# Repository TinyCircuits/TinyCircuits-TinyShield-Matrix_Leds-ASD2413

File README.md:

# TinyCircuits TinyShield Matrix LEDs
# ASD2413 Rev2

The design files are located under design_files/ for the TinyCircuits ASD2413 Rev 2 PCB.  This is a Tiny shield board (Square Version, 20mm x 20mm) that has a 54 LEDs in a 6x9 Matrix.

Format is in Cadsoft Eagle format - Eagle version 6.2 was used for the original design.

For more infomation on this, check out the product page at TinyCircuits.com:  https://tinycircuits.com/collections/leds-displays/products/matrix-led-tinyshield

# License:

Design by TinyCircuits.
All design files are released under the Creative Commons Attribution Share-Alike 3.0 License, see the following link for details: http://creativecommons.org/licenses/by-sa/3.0

All text above must be included in any redistribution or derived design

This project uses designs and concepts developed as part of the Arduino project and the LilyPad project.  The TinyCircuits design files themselves (schematics, PCB and libraries) are not directly derived from these works' design files and have been created new, however the concepts and basic architecture behind the TinyDuino and TinyLily products are derived and we thank the hard work of the organizations below for their contributions to open-source hardware:
  
Original Arduino Uno Design by Team Arduino

LilyPad Arduino Design by Leah Buechley and Sparkfun Electronics

Please support the open-source hardware community

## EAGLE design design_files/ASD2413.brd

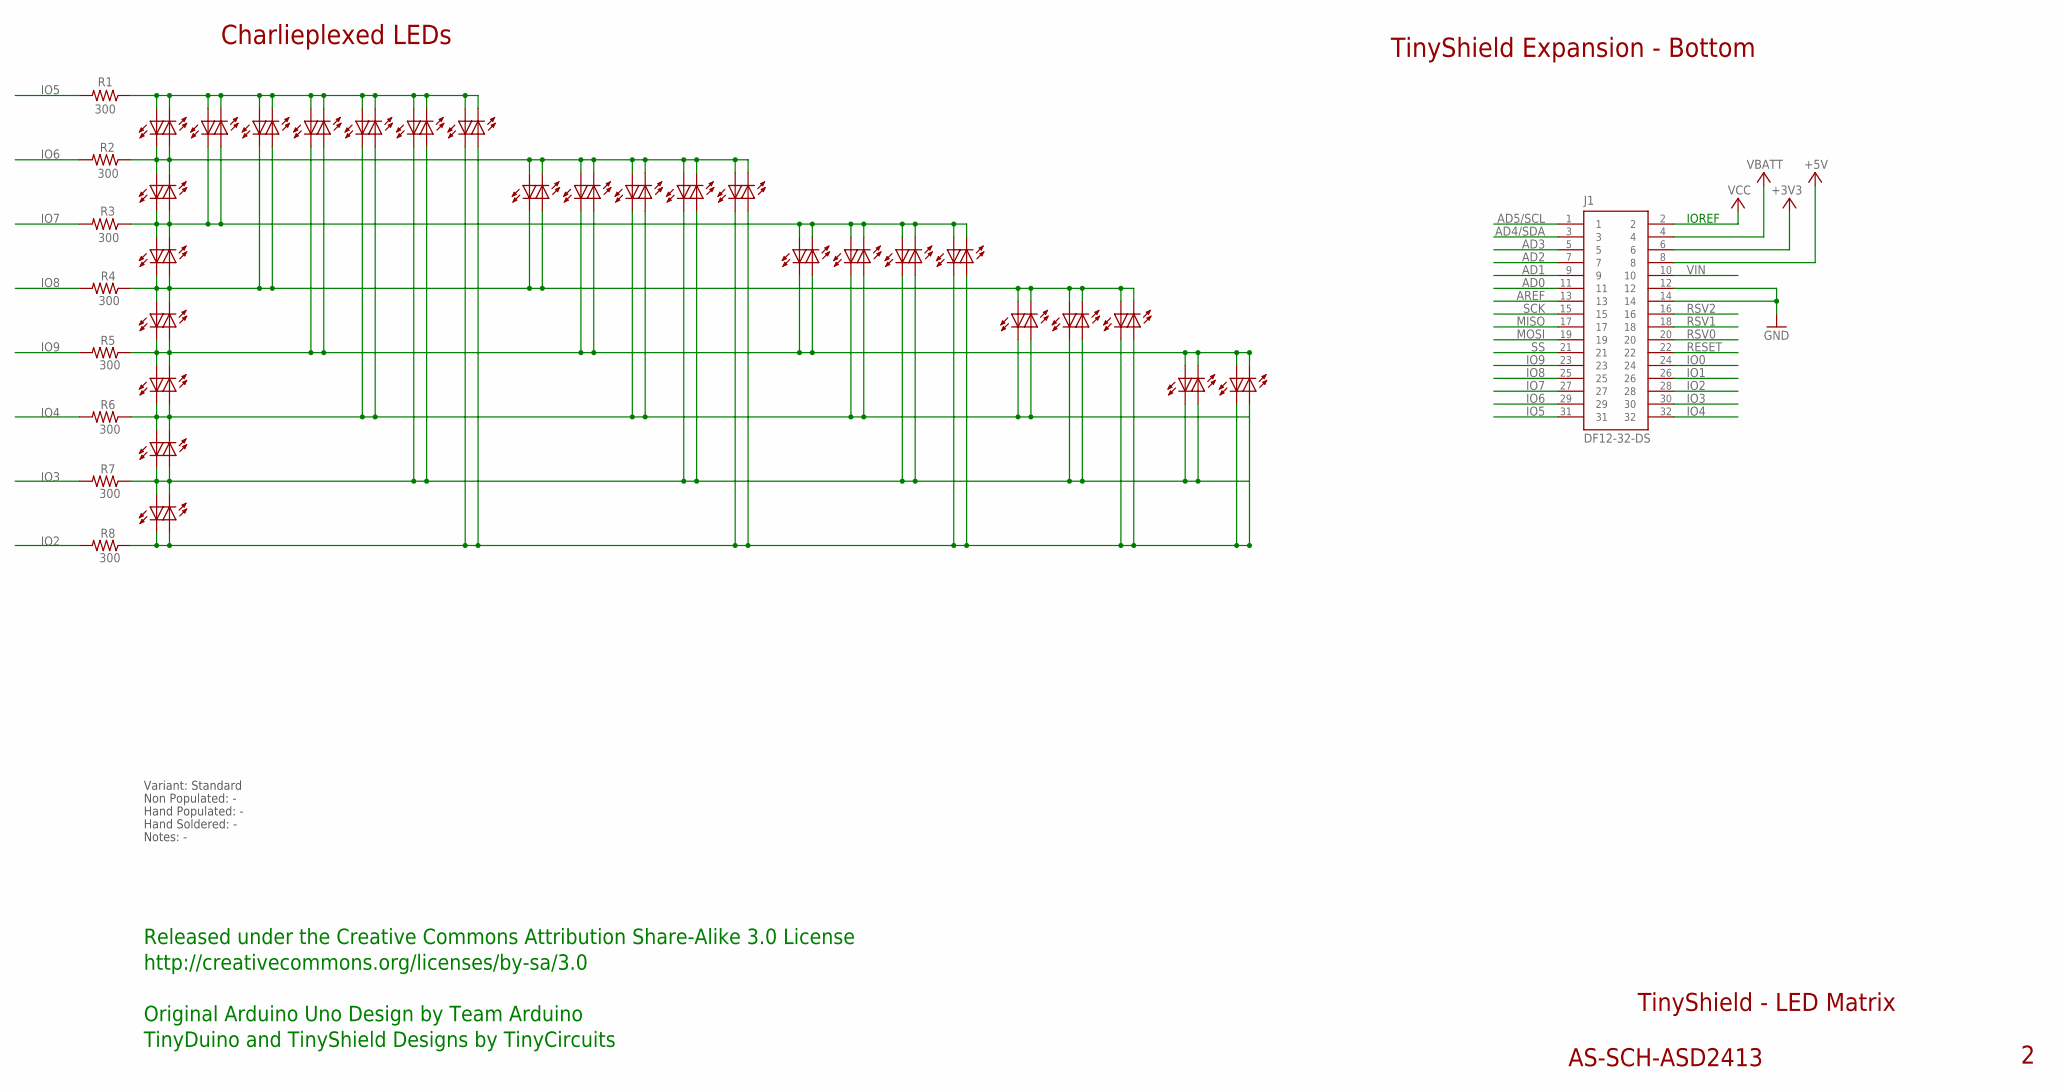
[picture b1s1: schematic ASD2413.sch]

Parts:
D1, D2, D3, D4, D5, D6, D7, D8, D9, D10, D11, D12, D13, D14, D15, D16, D17, D18, D19, D20, D21, D22, D23, D24, D25, D26, D27, D28, D29, D30, D31, D32, D33, D34, D35, D36, D37, D38, D39, D40, D41, D42, D43, D44, D45, D46, D47, D48, D49, D50, D51, D52, D53, D54: GREEN; 0402_LED; PARTNO AS-ITM-00038
J1: DF12-32-DS; PARTNO AS-ITM-00012
R1, R6, R7, R8: 300; 0402; PARTNO AS-ITM-00016
R2, R3, R4, R5: 300; 0402

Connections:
+3V3: J1.6
+5V: J1.8
AD0: J1.11
AD1: J1.9
AD2: J1.7
AD3: J1.5
AD4/SDA: J1.3
AD5/SCL: J1.1
AREF: J1.13
GND: J1.12, J1.14
IO0: J1.24
IO1: J1.26
IO2: J1.28, R8.2
IO3: J1.30, R7.2
IO4: J1.32, R6.2
IO5: J1.31, R1.2
IO6: J1.29, R2.2
IO7: J1.27, R3.2
IO8: J1.25, R4.2
IO9: J1.23, R5.2
MISO: J1.17
MOSI: J1.19
unnamed: D1.2 (C), D2.1 (A), D8.1 (A), D9.2 (C), D27.1 (A), D28.2 (C), D29.1 (A), D30.2 (C), D31.1 (A), D32.2 (C), D33.1 (A), D34.2 (C), D35.1 (A), D36.2 (C), R2.1
unnamed: D3.2 (C), D4.1 (A), D10.1 (A), D11.2 (C), D17.2 (C), D18.1 (A), D27.2 (C), D28.1 (A), D45.1 (A), D46.2 (C), D47.1 (A), D48.2 (C), D49.1 (A), D50.2 (C), R4.1
unnamed: D5.2 (C), D6.1 (A), D12.1 (A), D13.2 (C), D21.2 (C), D22.1 (A), D31.2 (C), D32.1 (A), D39.2 (C), D40.1 (A), D45.2 (C), D46.1 (A), R6.1
unnamed: D7.2 (C), D14.1 (A), D25.2 (C), D26.1 (A), D35.2 (C), D36.1 (A), D43.2 (C), D44.1 (A), D49.2 (C), D50.1 (A), D53.2 (C), D54.1 (A), R8.1
unnamed: D1.1 (A), D8.2 (C), D15.1 (A), D16.2 (C), D17.1 (A), D18.2 (C), D19.1 (A), D20.2 (C), D21.1 (A), D22.2 (C), D23.1 (A), D24.2 (C), D25.1 (A), D26.2 (C), R1.1
unnamed: D2.2 (C), D3.1 (A), D9.1 (A), D10.2 (C), D15.2 (C), D16.1 (A), D37.1 (A), D38.2 (C), D39.1 (A), D40.2 (C), D41.1 (A), D42.2 (C), D43.1 (A), D44.2 (C), R3.1
unnamed: D6.2 (C), D7.1 (A), D13.1 (A), D14.2 (C), D23.2 (C), D24.1 (A), D33.2 (C), D34.1 (A), D41.2 (C), D42.1 (A), D47.2 (C), D48.1 (A), D51.2 (C), D52.1 (A), R7.1
unnamed: D4.2 (C), D5.1 (A), D11.1 (A), D12.2 (C), D19.2 (C), D20.1 (A), D29.2 (C), D30.1 (A), D37.2 (C), D38.1 (A), D51.1 (A), D52.2 (C), D53.1 (A), D54.2 (C), R5.1
RESET: J1.22
RSV0: J1.20
RSV1: J1.18
RSV2: J1.16
SCK: J1.15
SS: J1.21
VBATT: J1.4
VCC: J1.2
VIN: J1.10

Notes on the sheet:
TinyShield Expansion - Bottom
Charlieplexed LEDs
TinyShield - LED Matrix
AS-SCH-ASD2413
IOREF
Released under the Creative Commons Attribution Share-Alike 3.0 License
http://creativecommons.org/licenses/by-sa/3.0
Original Arduino Uno Design by Team Arduino
TinyDuino and TinyShield Designs by TinyCircuits
Variant: Standard
Non Populated: -
Hand Populated: -
Hand Soldered: -
Notes: -

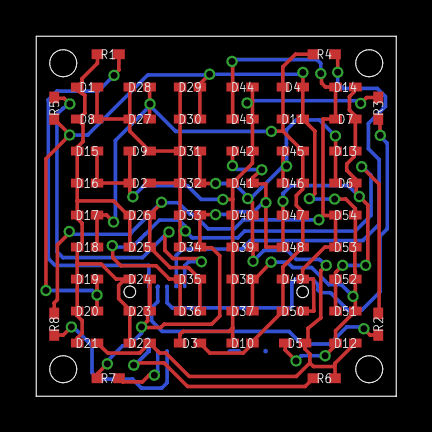
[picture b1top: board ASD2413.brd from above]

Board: 2 copper layers, 20.0 x 20.0 mm, 64 parts (1 on the bottom side), 17 nets.

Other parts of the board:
U$1: DOCFIELD-TINYCIRCUITS-PCB

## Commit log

2014-08-24 Updated Link
2019-01-02 update format
2019-01-07 updated comments
2019-01-10 added tutorial images
2019-01-11 updated pictures
2019-01-11 add .zip files
2019-01-11 updated images
2019-05-20 updated naming
2019-05-22 added library .zip files
2019-05-22 added images
2019-08-12 fix examples
2019-08-12 fix libraries
2019-08-12 Someone misspelled Charlieplexing and now it must remain like this
2020-02-11 image update
2020-07-28 Add CAD data
2020-08-14 Update CAD drawing
